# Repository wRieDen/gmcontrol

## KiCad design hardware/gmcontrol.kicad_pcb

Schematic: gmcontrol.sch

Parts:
J1: USB_OTG; USB_Micro-B
J2: Jack-DC; BarrelJack_Horizontal_modified
J3, J11, J12, J13, J14, J15, J16, J17, J18, J19, J20, J21, J22, J23, J24, J25, J26: Conn_01x01; 1.27Pad
J4: Screw_Terminal_01x04; TerminalBlock_bornier-4_P5.08mm
J5, J6, J7, J8, J9, J10: Conn_01x01; 2.54Pad
MK1, MK2: Mounting_Hole_PAD; MountingHole_2.2mm_M2_ISO7380_Pad

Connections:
/controller/BOOT0: J12.1; also elsewhere on the board
/controller/GND: J1.5, J1.6, J2.2, J2.3, J3.1, J10.1, J11.1, MK1.1, MK2.1; also elsewhere on the board
/controller/PA7: J13.1; also elsewhere on the board
/controller/PA15: J14.1; also elsewhere on the board
/controller/PB0: J15.1; also elsewhere on the board
/controller/PB1: J16.1; also elsewhere on the board
/controller/PB2: J17.1; also elsewhere on the board
/controller/PB3: J18.1; also elsewhere on the board
/controller/PB4: J19.1; also elsewhere on the board
/controller/PB5: J20.1; also elsewhere on the board
/controller/PB6: J8.1; also elsewhere on the board
/controller/PB7: J9.1; also elsewhere on the board
/controller/PB12: J21.1; also elsewhere on the board
/controller/PC13: J22.1; also elsewhere on the board
/controller/PC14: J23.1; also elsewhere on the board
/controller/PC15: J24.1; also elsewhere on the board
/controller/RESET: J7.1; also elsewhere on the board
/controller/SWDCLK: J6.1; also elsewhere on the board
/controller/SWDIO: J5.1; also elsewhere on the board
/controller/USB_DM: J1.2; also elsewhere on the board
/controller/USB_DP: J1.3; also elsewhere on the board
/gate_voltage_supply/VIN: J2.1; also elsewhere on the board
/power/3.3V: J25.1, J26.1; also elsewhere on the board
/power/Vusb: J1.1; also elsewhere on the board

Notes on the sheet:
General Motor Controller - 4 Phases - 3 to 30V - 0 to 100% Duty Cycle - USB

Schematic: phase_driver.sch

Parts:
C1, C2: 1u; 0603_Small
Q1, Q2, Q3, Q5: BC817; SOT-23_Small
Q4, Q6: BC807; SOT-23_Small
Q7, Q8: AON7212; DFN3x3A_8L_EP1_P
R1, R2, R3, R5: 470; 0603_Small
R4: 100; 0603_Small
R6: 10k; 0603_Small
R7: 1k; 0603_Small

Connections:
/controller/GND: C1.2, C2.2, Q2.2, Q4.3, Q6.3, Q8.1, R4.2, R7.2; also elsewhere on the board
/controller/PHASE_1_H: R1.2; also elsewhere on the board
/controller/PHASE_1_L: R2.2; also elsewhere on the board
/gate_voltage_supply/VIN: Q7.3; also elsewhere on the board
/gate_voltage_supply/Vgh: C2.1, Q3.3, R3.1; also elsewhere on the board
/gate_voltage_supply/Vgl: C1.1, Q5.3, R5.1; also elsewhere on the board
/phase_driver_1/PHASE: Q7.1, Q8.3, R6.2
/phase_driver_1/SENSE: R6.1, R7.1; also elsewhere on the board
unnamed: Q1.1, R1.1
unnamed: Q1.2, R4.1
unnamed: Q1.3, Q3.1, Q4.1, R3.2
unnamed: Q2.1, R2.1
unnamed: Q2.3, Q5.1, Q6.1, R5.2
unnamed: Q3.2, Q4.2, Q7.2
unnamed: Q5.2, Q6.2, Q8.2

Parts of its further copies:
C11, C12, C13, C14, C15, C16: 1u; 0603_Small
Q9, Q10, Q11, Q13, Q17, Q18, Q19, Q21, Q25, Q26, Q27, Q29: BC817; SOT-23_Small
Q12, Q14, Q20, Q22, Q28, Q30: BC807; SOT-23_Small
Q15, Q16, Q23, Q24, Q31, Q32: AON7212; DFN3x3A_8L_EP1_P
R11, R12, R13, R15, R18, R19, R20, R22, R25, R26, R27, R29: 470; 0603_Small
R14, R21, R28: 100; 0603_Small
R16, R23, R30: 10k; 0603_Small
R17, R24, R31: 1k; 0603_Small

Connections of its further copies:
/controller/GND: C11.2, C12.2, C13.2, C14.2, C15.2, C16.2, Q10.2, Q12.3, Q14.3, Q16.1, Q18.2, Q20.3, Q22.3, Q24.1, Q26.2, Q28.3, Q30.3, Q32.1, R14.2, R17.2, R21.2, R24.2, R28.2, R31.2; also elsewhere on the board
/controller/PHASE_2_H: R11.2; also elsewhere on the board
/controller/PHASE_2_L: R12.2; also elsewhere on the board
/controller/PHASE_3_H: R18.2; also elsewhere on the board
/controller/PHASE_3_L: R19.2; also elsewhere on the board
/controller/PHASE_4_H: R25.2; also elsewhere on the board
/controller/PHASE_4_L: R26.2; also elsewhere on the board
/gate_voltage_supply/VIN: Q15.3, Q23.3, Q31.3; also elsewhere on the board
/gate_voltage_supply/Vgh: C12.1, C14.1, C16.1, Q11.3, Q19.3, Q27.3, R13.1, R20.1, R27.1; also elsewhere on the board
/gate_voltage_supply/Vgl: C11.1, C13.1, C15.1, Q13.3, Q21.3, Q29.3, R15.1, R22.1, R29.1; also elsewhere on the board
/sheet5AEA1DE6/PHASE: Q15.1, Q16.3, R16.2
/sheet5AEA1DE6/SENSE: R16.1, R17.1; also elsewhere on the board
/sheet5AEA2A39/PHASE: Q23.1, Q24.3, R23.2
/sheet5AEA2A39/SENSE: R23.1, R24.1; also elsewhere on the board
/sheet5AEA3194/PHASE: Q31.1, Q32.3, R30.2
/sheet5AEA3194/SENSE: R30.1, R31.1; also elsewhere on the board
unnamed: Q9.1, R11.1
unnamed: Q9.2, R14.1
unnamed: Q10.1, R12.1
unnamed: Q10.3, Q13.1, Q14.1, R15.2
unnamed: Q9.3, Q11.1, Q12.1, R13.2
unnamed: Q11.2, Q12.2, Q15.2
unnamed: Q13.2, Q14.2, Q16.2
unnamed: Q17.1, R18.1
unnamed: Q17.2, R21.1
unnamed: Q17.3, Q19.1, Q20.1, R20.2
unnamed: Q18.1, R19.1
unnamed: Q18.3, Q21.1, Q22.1, R22.2
unnamed: Q19.2, Q20.2, Q23.2
unnamed: Q21.2, Q22.2, Q24.2
unnamed: Q25.1, R25.1
unnamed: Q25.2, R28.1
unnamed: Q25.3, Q27.1, Q28.1, R27.2
unnamed: Q26.1, R26.1
unnamed: Q26.3, Q29.1, Q30.1, R29.2
unnamed: Q27.2, Q28.2, Q31.2
unnamed: Q29.2, Q30.2, Q32.2

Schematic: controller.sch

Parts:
C3, C4: 10p; 0603_Small
C5, C6, C7, C8: 100n; 0603_Small
C9, C10: 47p; 0603_Small
R8, R9: 22R; 0603_Small
R10: 1.5k; 0603_Small
U1: STM32F103C8Tx; LQFP-48_7x7mm_P0.5mm
Y1: 16Mhz; Crystal_SMD_3225-4Pin_3.2x2.5mm

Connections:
/controller/BOOT0: U1.44; also elsewhere on the board
/controller/CLK_Vgh: U1.45; also elsewhere on the board
/controller/CLK_Vgl: U1.46; also elsewhere on the board
/controller/GND: C3.2, C4.2, C5.2, C6.2, C7.2, C8.2, C9.1, C10.2, U1.8, U1.23, U1.35, U1.47, Y1.2, Y1.4; also elsewhere on the board
/controller/PA7: U1.17; also elsewhere on the board
/controller/PA15: U1.38; also elsewhere on the board
/controller/PB0: U1.18; also elsewhere on the board
/controller/PB1: U1.19; also elsewhere on the board
/controller/PB2: U1.20; also elsewhere on the board
/controller/PB3: U1.39; also elsewhere on the board
/controller/PB4: U1.40; also elsewhere on the board
/controller/PB5: U1.41; also elsewhere on the board
/controller/PB6: U1.42; also elsewhere on the board
/controller/PB7: U1.43; also elsewhere on the board
/controller/PB12: U1.25; also elsewhere on the board
/controller/PC13: U1.2; also elsewhere on the board
/controller/PC14: U1.3; also elsewhere on the board
/controller/PC15: U1.4; also elsewhere on the board
/controller/PHASE_1_H: U1.29; also elsewhere on the board
/controller/PHASE_1_L: U1.26; also elsewhere on the board
/controller/PHASE_2_H: U1.30; also elsewhere on the board
/controller/PHASE_2_L: U1.27; also elsewhere on the board
/controller/PHASE_3_H: U1.31; also elsewhere on the board
/controller/PHASE_3_L: U1.28; also elsewhere on the board
/controller/PHASE_4_H: U1.21; also elsewhere on the board
/controller/PHASE_4_L: U1.22; also elsewhere on the board
/controller/RESET: U1.7; also elsewhere on the board
/controller/SENSE_Vgh: U1.14; also elsewhere on the board
/controller/SENSE_Vgl: U1.15; also elsewhere on the board
/controller/SENSE_Vmotor: U1.16; also elsewhere on the board
/controller/SWDCLK: U1.37; also elsewhere on the board
/controller/SWDIO: U1.34; also elsewhere on the board
/controller/USB_DM: C9.2, R8.2; also elsewhere on the board
/controller/USB_DP: C10.1, R9.2, R10.1; also elsewhere on the board
/phase_driver_1/SENSE: U1.10; also elsewhere on the board
/power/3.3V: C5.1, C6.1, C7.1, C8.1, R10.2, U1.1, U1.9, U1.24, U1.36, U1.48; also elsewhere on the board
/sheet5AEA1DE6/SENSE: U1.11; also elsewhere on the board
/sheet5AEA2A39/SENSE: U1.12; also elsewhere on the board
/sheet5AEA3194/SENSE: U1.13; also elsewhere on the board
unnamed: C3.1, U1.5, Y1.1
unnamed: C4.1, U1.6, Y1.3
unnamed: R8.1, U1.32
unnamed: R9.1, U1.33

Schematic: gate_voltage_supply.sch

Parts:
C17, C18: 22u; 0805_Small
D1, D2: 1N5819; D_SOD-323
D3, D4: 18V; D_SOD-323
L1, L2: 100u; CD32
Q33: BSS138; SOT-23_Small
Q34: BC817; SOT-23_Small
Q35: BSS84; SOT-23_Small
R32, R33, R36: 220; 0603_Small
R34, R39: 10k; 0603_Small
R35, R38, R40: 1k; 0603_Small
R37: 22k; 0603_Small

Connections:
/controller/CLK_Vgh: R32.2; also elsewhere on the board
/controller/CLK_Vgl: R33.2; also elsewhere on the board
/controller/GND: C18.2, D2.2 (A), D4.2, Q33.2, R34.2, R36.2, R38.2, R40.2; also elsewhere on the board
/controller/SENSE_Vgh: R37.2, R38.1; also elsewhere on the board
/controller/SENSE_Vgl: R39.2, R40.1; also elsewhere on the board
/gate_voltage_supply/VIN: C17.2, D3.2, L1.1; also elsewhere on the board
/gate_voltage_supply/Vgh: C17.1, D1.1 (K), D3.1, Q35.2, R35.1, R37.1; also elsewhere on the board
/gate_voltage_supply/Vgl: C18.1, D4.1, L2.2, R39.1; also elsewhere on the board
unnamed: D1.2 (A), L1.2, Q33.3
unnamed: D2.1 (K), L2.1, Q35.3
unnamed: Q33.1, R32.1, R34.1
unnamed: Q34.1, R33.1
unnamed: Q34.2, R36.1
unnamed: Q34.3, Q35.1, R35.2

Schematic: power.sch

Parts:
C19, C21, C22, C23, C25, C26, C27, C28, C29, C30: 22u; 0805_Small
C20: 100n; 0603_Small
C24: 22u; 0603_Small
Q36: AO3401; SOT-23_Small
R41, R42: 10k; 0603_Small
R43: 1k; 0603_Small
U2: HT7333-1; SOT-89-3

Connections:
/controller/GND: C19.1, C20.2, C21.1, C22.1, C23.1, C24.2, C25.1, C26.1, C27.1, C28.1, C29.1, C30.1, R41.1, R42.2, U2.1 (GND); also elsewhere on the board
/controller/SENSE_Vmotor: R42.1, R43.1; also elsewhere on the board
/gate_voltage_supply/VIN: C19.2, C20.1, C21.2, C22.2, C23.2, C25.2, C26.2, C27.2, C28.2, C29.2, C30.2, Q36.1, Q36.2, R41.2, R43.2, U2.2 (VI); also elsewhere on the board
/power/3.3V: C24.1, U2.3 (VO); also elsewhere on the board
/power/Vusb: Q36.3; also elsewhere on the board

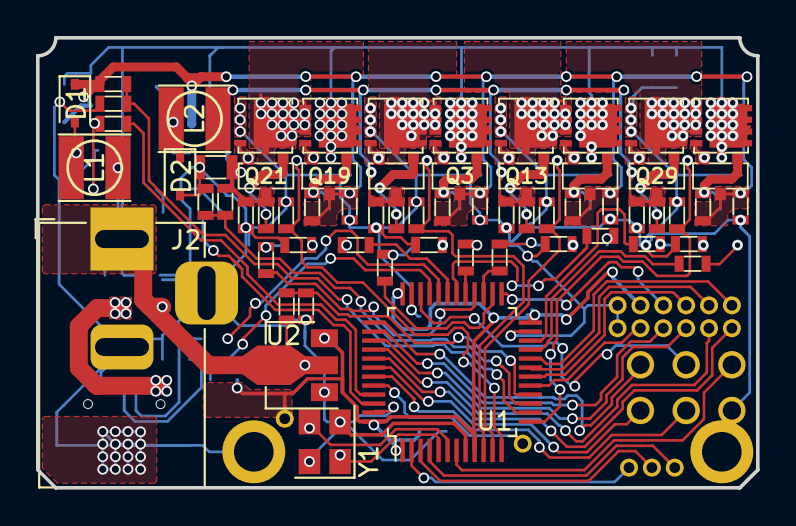
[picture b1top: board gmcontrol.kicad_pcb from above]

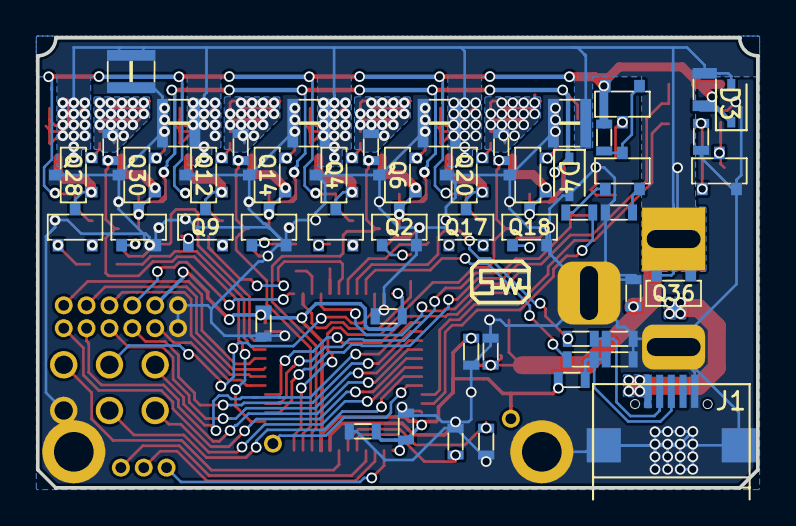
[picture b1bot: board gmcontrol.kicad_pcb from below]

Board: 2 copper layers, 40.0 x 25.0 mm, 145 parts (56 on the bottom side), 85 nets.

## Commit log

2018-04-30 initial
2018-05-01 vgate, fet driver
2018-05-01 ignore .raw and .log
2018-05-01 power, mcu
2018-05-02 phase routet
2018-05-03 change to kicad 5
2018-05-04 smaller footprints
2018-05-04 motor layout
2018-05-05 multiple phases
2018-05-05 power layout
2018-05-05 basic layout
2018-05-06 stm layout
2018-05-06 finished pcb design
2018-05-06 add logo
2018-05-06 Ordered V1 PCB version
2018-07-12 cube project
2018-07-12 ignore
2018-07-12 ignore build, generic makefile
2018-11-08 kicad5-stable
